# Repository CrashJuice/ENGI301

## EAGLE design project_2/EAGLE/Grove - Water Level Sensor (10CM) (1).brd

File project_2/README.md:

PocketBeagle-Based PCB Project

Overview

This project involves designing and building a PCB around the PocketBeagle to implement a system with specific features and functionality. The goal is to integrate multiple components, such as LEDs, sensors, and input devices, into a compact, reliable circuit for demonstration and testing purposes.

Features

PocketBeagle Integration: Serves as the microcontroller for the project.

Custom PCB Design: A compact and efficient layout that includes connections for multiple hardware components.

Visual Indicators: Use of LEDs for feedback and status indication.

User Interaction: Includes buttons or other input methods to interface with the system.

Components

PocketBeagle: Acts as the central processing unit.

LEDs: Provide visual feedback for system status.

Button(s): Allow for user interaction with the system.

Buzzer (Optional): Can be included for auditory feedback.

Additional Sensors/Modules: Depending on the specific use case, additional sensors can be integrated.

Functionality

Hardware Integration:

All components are connected to the PocketBeagle via GPIO pins or other interfaces (e.g., I2C, SPI, UART).

The PCB provides a stable and organized connection environment.

Feedback System:

LEDs indicate system states such as power, activity, or errors.

Buttons allow users to trigger specific actions or reset the system.

Software Control:

The PocketBeagle runs scripts to manage hardware components.

Scripts handle real-time inputs and outputs for smooth operation.

PCB Design

Schematic:

The schematic includes all connections between components, showing how they interface with the PocketBeagle.

Important connections are labeled (e.g., P2_4, P2_6 for LEDs).

Board Layout:

The PCB layout is designed for compactness and minimal signal interference.

Includes clear labels for pin headers and component placement.

Acknowledgements:

I used Groove Water Sensor base PCB design to create mine link to their website here: https://wiki.seeedstudio.com/Grove-Water_Sensor/

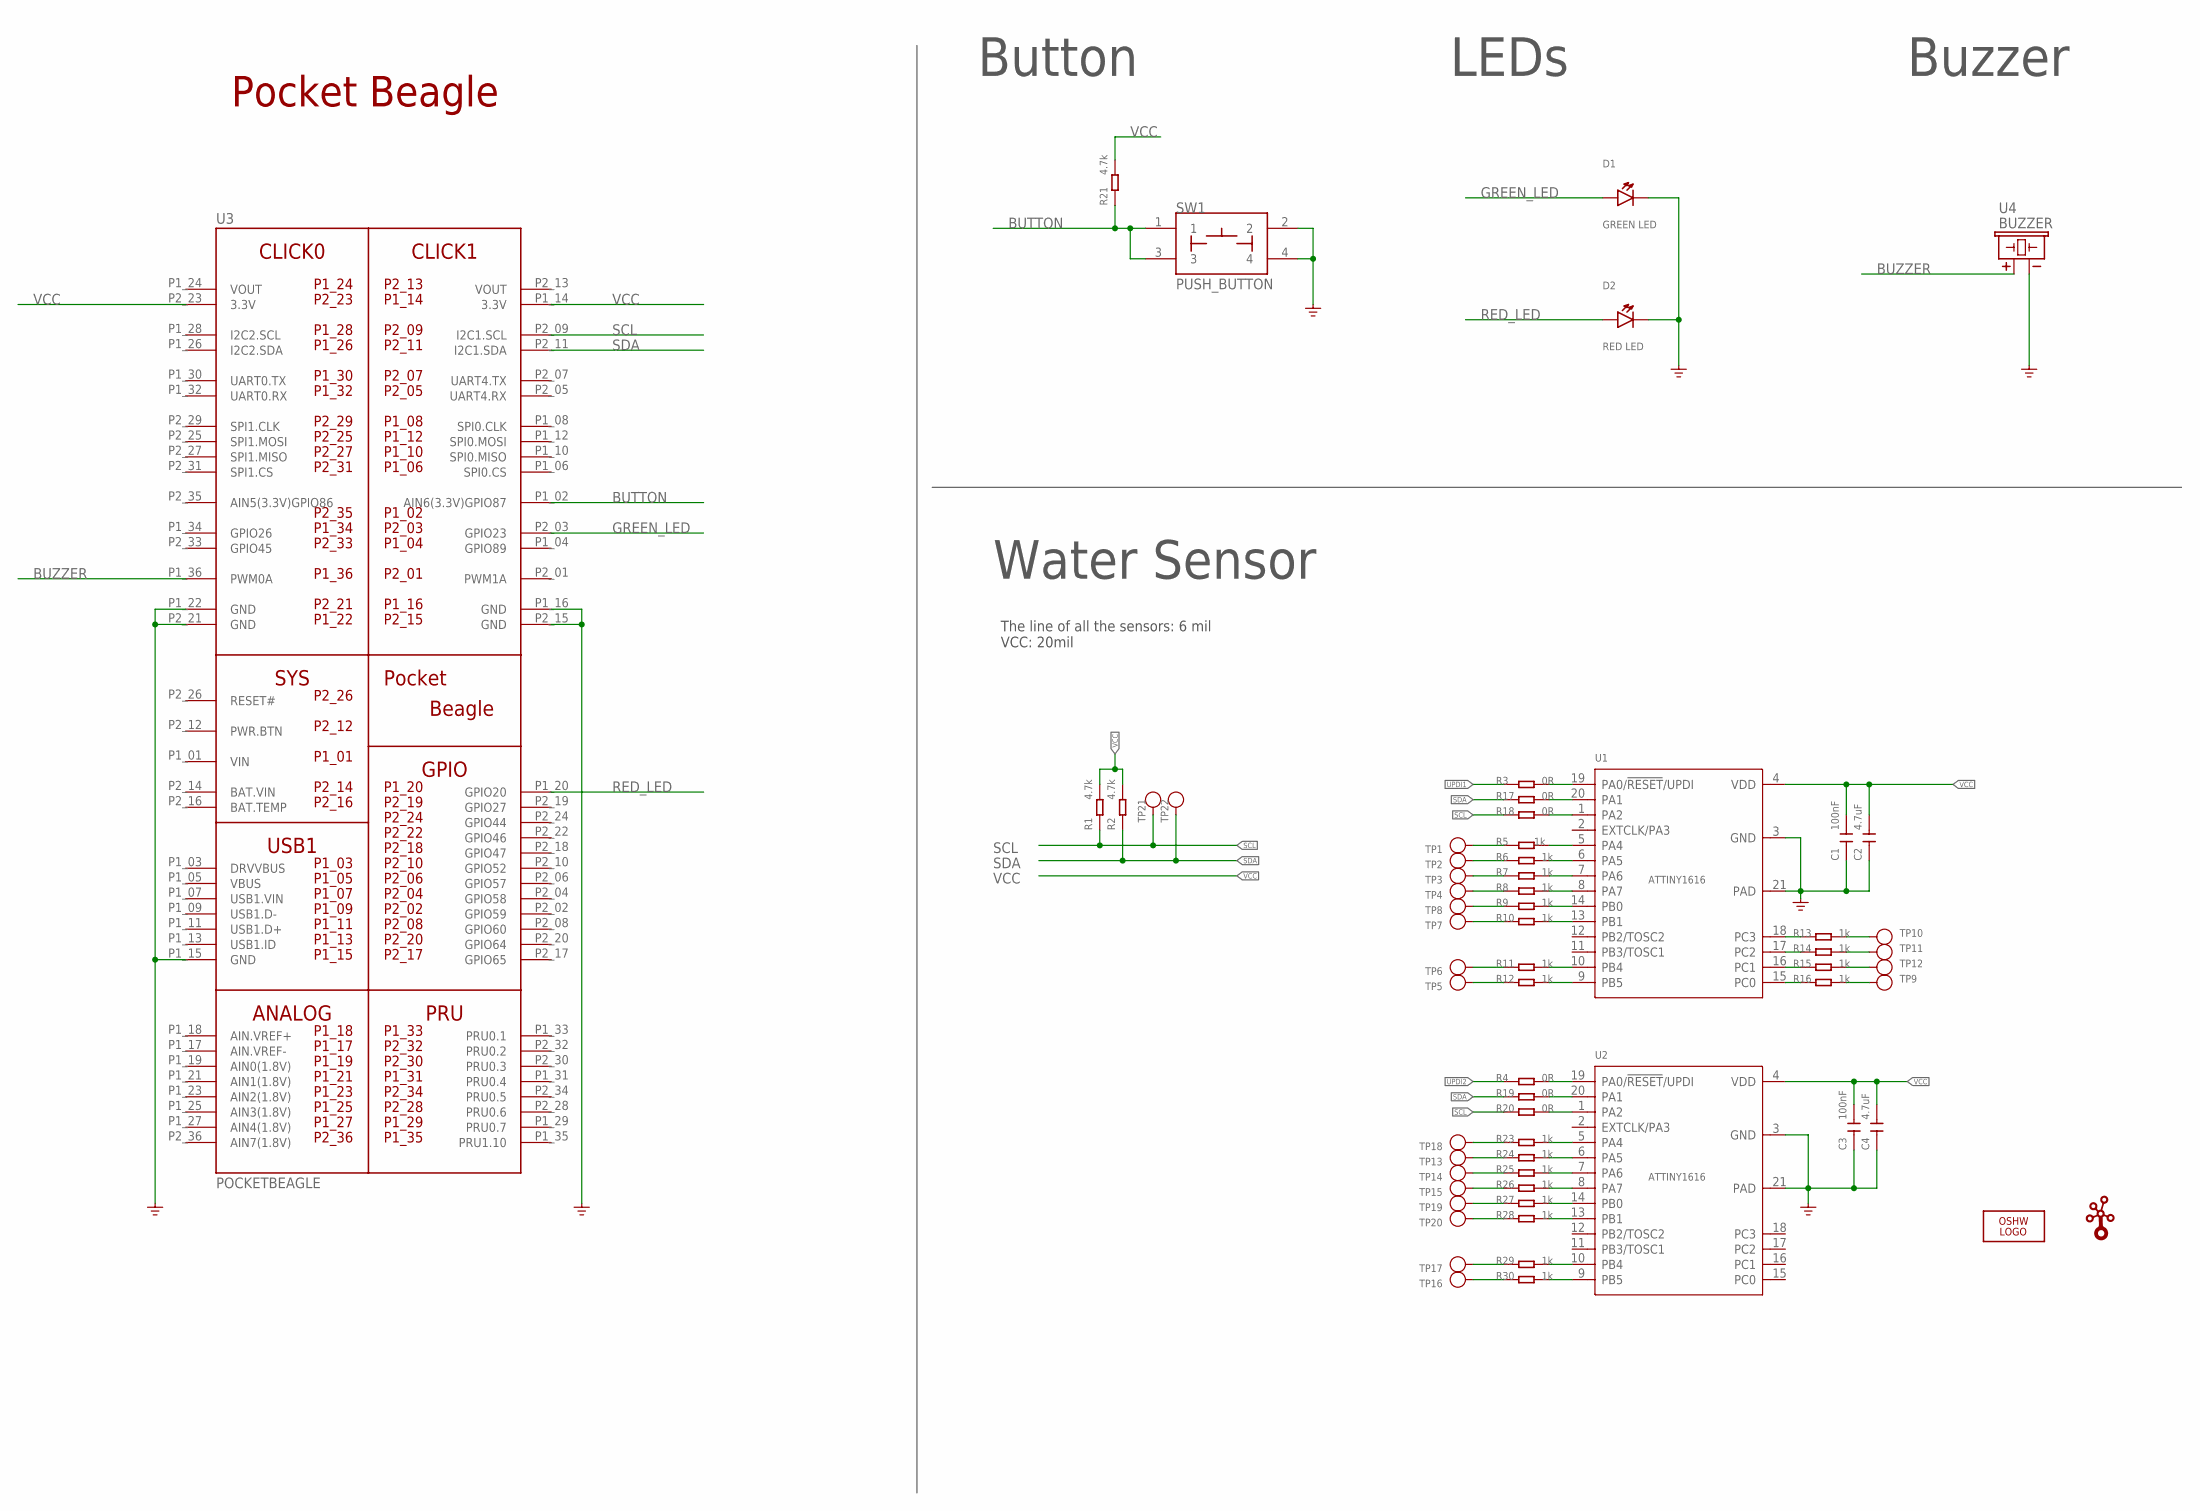
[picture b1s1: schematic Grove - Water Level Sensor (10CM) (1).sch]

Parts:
C1, C3: 100nF; C0402
C2, C4: 4.7uF; C0402
D1: GREEN LED; EIA-STD
D2: RED LED; EIA-STD
LOGO2: LOGO-OSHW-FILLX0200-NT; OSHW_FILLX200_NOTEXT
R1, R2, R21: 4.7k; R0402
R3, R4, R17, R18, R19, R20: 0R; R0402
R5, R6, R7, R8, R9, R10, R11, R12, R13, R14, R15, R16, R23, R24, R25, R26, R27, R28, R29, R30: 1k; R0402
SW1: PUSH_BUTTON; BUTTON_12.5MM
TP1, TP2, TP3, TP4, TP5, TP6, TP7, TP8, TP9, TP10, TP11, TP12, TP13, TP14, TP15, TP16, TP17, TP18, TP19, TP20: senser; TP-80X40MIL-NOSTOP
TP21, TP22: test; TP-D45MIL
U1, U2: ATTINY1616; VQFN20-0.4-3X3MM
U3: POCKETBEAGLE
U4: BUZZER; BUZZER_6.5MM
U$2: LOGO-GROVE; GROVE-SILK-BIG

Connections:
BAT.VIN: U3.P2_14 (BAT.VIN)
BUTTON: R21.1, SW1.1, SW1.3, U3.P1_02 (AIN6(3.3V)GPIO87)
BUZZER: U3.P1_36 (PWM0A), U4.+
GND: C1.1, C2.1, C3.1, C4.1, D1.CATHODE, D2.CATHODE, SW1.2, SW1.4, U1.3 (GND), U1.21 (PAD), U2.3 (GND), U2.21 (PAD), U3.P1_15 (GND), U3.P1_16 (GND), U3.P1_22 (GND), U3.P2_15 (GND), U3.P2_21 (GND), U4.-
GREEN_LED: D1.ANODE, U3.P2_03 (GPIO23)
unnamed: R3.2, U1.19 (PA0/!RESET!/UPDI)
unnamed: R4.2, U2.19 (PA0/!RESET!/UPDI)
unnamed: R17.2, U1.20 (PA1)
unnamed: R18.2, U1.1 (PA2)
unnamed: R19.2, U2.20 (PA1)
unnamed: R20.2, U2.1 (PA2)
unnamed: R23.1, TP18.P$1
unnamed: R29.1, TP17.P$1
unnamed: R30.2, U2.9 (PB5)
unnamed: R29.2, U2.10 (PB4)
unnamed: R28.2, U2.13 (PB1)
unnamed: R27.2, U2.14 (PB0)
unnamed: R26.2, U2.8 (PA7)
unnamed: R25.2, U2.7 (PA6)
unnamed: R24.2, U2.6 (PA5)
unnamed: R23.2, U2.5 (PA4)
unnamed: R28.1, TP20.P$1
unnamed: R27.1, TP19.P$1
unnamed: R5.2, U1.5 (PA4)
unnamed: R6.2, U1.6 (PA5)
unnamed: R7.2, U1.7 (PA6)
unnamed: R8.2, U1.8 (PA7)
unnamed: R9.2, U1.14 (PB0)
unnamed: R10.2, U1.13 (PB1)
unnamed: R25.1, TP14.P$1
unnamed: R11.2, U1.10 (PB4)
unnamed: R12.2, U1.9 (PB5)
unnamed: R13.1, U1.18 (PC3)
unnamed: R14.1, U1.17 (PC2)
unnamed: R15.1, U1.16 (PC1)
unnamed: R16.1, U1.15 (PC0)
unnamed: R11.1, TP6.P$1
unnamed: R12.1, TP5.P$1
unnamed: R26.1, TP15.P$1
unnamed: R30.1, TP16.P$1
unnamed: R10.1, TP7.P$1
unnamed: R9.1, TP8.P$1
unnamed: R24.1, TP13.P$1
unnamed: R13.2, TP10.P$1
unnamed: R14.2, TP11.P$1
unnamed: R15.2, TP12.P$1
unnamed: R5.1, TP1.P$1
unnamed: R6.1, TP2.P$1
unnamed: R7.1, TP3.P$1
unnamed: R8.1, TP4.P$1
unnamed: R16.2, TP9.P$1
RED_LED: D2.ANODE, U3.P1_20 (GPIO20)
SCL: R1.1, R18.1, R20.1, TP21.T, U3.P2_09 (I2C1.SCL)
SDA: R2.1, R17.1, R19.1, TP22.T, U3.P2_11 (I2C1.SDA)
UPDI1: R3.1
UPDI2: R4.1
VCC: C1.2, C2.2, C3.2, C4.2, R1.2, R2.2, R21.2, U1.4 (VDD), U2.4 (VDD), U3.P1_14 (3.3V), U3.P2_23 (3.3V)
VIN: U3.P1_01 (VIN)
VOUT: U3.P1_24 (VOUT), U3.P2_13 (VOUT)

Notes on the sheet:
The line of all the sensors: 6 mil VCC: 20mil
Water Sensor
Button
LEDs
Buzzer
Pocket Beagle

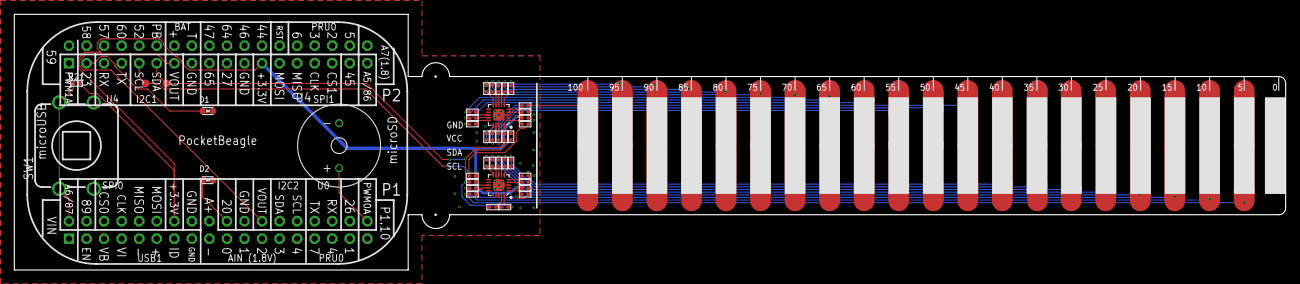
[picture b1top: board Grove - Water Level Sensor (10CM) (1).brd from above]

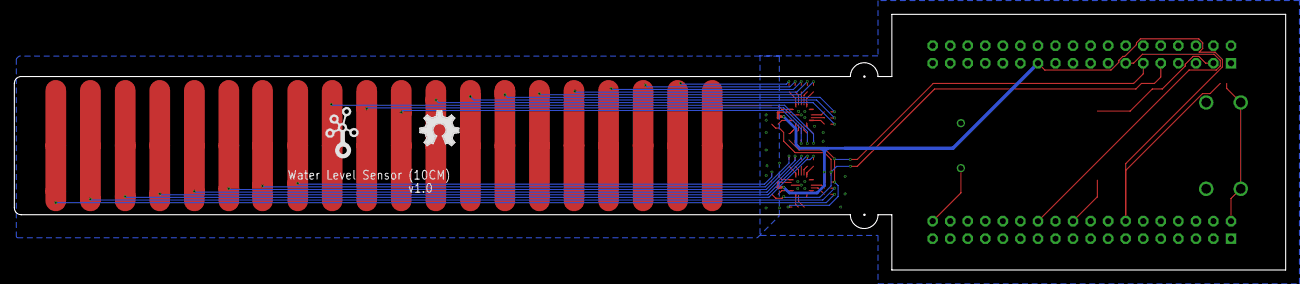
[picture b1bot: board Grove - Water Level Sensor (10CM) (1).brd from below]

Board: 2 copper layers, 184.0 x 37.0 mm, 64 parts (2 on the bottom side), 55 nets.

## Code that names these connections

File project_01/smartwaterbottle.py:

# -*- coding: utf-8 -*-
"""
--------------------------------------------------------------------------
Aquatrac smart water bottle
--------------------------------------------------------------------------
License:   
Copyright 2024 Juan Aizprua

Redistribution and use in source and binary forms, with or without 
modification, are permitted provided that the following conditions are met:

1. Redistributions of source code must retain the above copyright notice, this 
list of conditions and the following disclaimer.

2. Redistributions in binary form must reproduce the above copyright notice, 
this list of conditions and the following disclaimer in the documentation 
and/or other materials provided with the distribution.

3. Neither the name of the copyright holder nor the names of its contributors 
may be used to endorse or promote products derived from this software without 
specific prior written permission.

THIS SOFTWARE IS PROVIDED BY THE COPYRIGHT HOLDERS AND CONTRIBUTORS "AS IS" 
AND ANY EXPRESS OR IMPLIED WARRANTIES, INCLUDING, BUT NOT LIMITED TO, THE 
IMPLIED WARRANTIES OF MERCHANTABILITY AND FITNESS FOR A PARTICULAR PURPOSE ARE 
DISCLAIMED. IN NO EVENT SHALL THE COPYRIGHT HOLDER OR CONTRIBUTORS BE LIABLE 
FOR ANY DIRECT, INDIRECT, INCIDENTAL, SPECIAL, EXEMPLARY, OR CONSEQUENTIAL 
DAMAGES (INCLUDING, BUT NOT LIMITED TO, PROCUREMENT OF SUBSTITUTE GOODS OR 
SERVICES; LOSS OF USE, DATA, OR PROFITS; OR BUSINESS INTERRUPTION) HOWEVER 
CAUSED AND ON ANY THEORY OF LIABILITY, WHETHER IN CONTRACT, STRICT LIABILITY, 
OR TORT (INCLUDING NEGLIGENCE OR OTHERWISE) ARISING IN ANY WAY OUT OF THE USE 
OF THIS SOFTWARE, EVEN IF ADVISED OF THE POSSIBILITY OF SUCH DAMAGE.
--------------------------------------------------------------------------
This file provides an interface to a PWM controllered buzzer.
  - Ex:  https://www.adafruit.com/product/1536


Combines water level sensor, buzzer, button, and leds together to create a program that helps you keep track of how much water you are drinking and if you 
are on track for the amount you should be drinking in a day.

"""








from button import Button
from led import LED
from buzzer import Buzzer
from waterlevelsensor import get_water_level
import Adafruit_BBIO.GPIO as GPIO
import time
import threading 



RED_LED_PIN = "P2_4"  # Red LED pin
GREEN_LED_PIN = "P2_6"  # Green LED pin
BUTTON_PIN = "P2_2"  # Button pin
BUZZER_PIN = "P2_1"  # Buzzer pin

red_led = LED(pin=RED_LED_PIN, low_off=True)  # Red LED, off when LOW
green_led = LED(pin=GREEN_LED_PIN, low_off=True)  # Green LED, off when LOW

# Initialize Button
button = Button(pin=BUTTON_PIN, sleep_time=0.1, active_low=True)

buzzer = Buzzer(pin=BUZZER_PIN) 

# Target water goal
TARGET_WATER = 100  # Target water intake in %

previous_water_level = 0.0  # Stores the last recorded water level
water_drunk = 0.0           # Amount of water consumed in percentage
faillasttime = False  # Tracks if user failed previously
minsections = 0  # Tracks the number of 30-minute sections

# Global variable to check progress (shared between monitor and button press)
def check_user_progress():
    global minsections, water_drunk, faillasttime
    
    required_intake = (minsections / 32) * TARGET_WATER  # Calculate required intake for this section
    
    if water_drunk >= required_intake:
        green_led.on()  # On track
        red_led.off()   # Turn off red LED
        time.sleep(10)
        green_led.off()  # Turn off green LED after 10 seconds
    else:
        green_led.off()  # Turn off green LED
        red_led.on()     # Behind
        time.sleep(10)
        red_led.off()    # Turn off red LED after 10 seconds

        if faillasttime:
            buzzer.play(800, 2.0, False)  # Play buzzer for 2 seconds
            time.sleep(2.0)
            buzzer.play(980, 2.0, True)   # Play buzzer again for 2 seconds
            time.sleep(2.0)

        faillasttime = True  # Mark that they failed this time

def button_press_check():
    """ Check button press and call check_user_progress() if pressed """
    if button.is_pressed():
        print("Button Pressed!")
        check_user_progress()

def check_water_level():
    global previous_water_level, water_drunk
    
    current_water_level = get_water_level()  # Get the current water level
    
    if current_water_level is not None:
        # If the current water level is lower than the previous one, calculate the difference
        if current_water_level < previous_water_level:
            water_drunk += previous_water_level - current_water_level  # Add the difference to water drunk
            
        previous_water_level = current_water_level  # Update previous water level to current
        
        print(f"Current water level: {current_water_level:.2f}%")
        print(f"Water drank: {water_drunk:.2f}%")
    else:
        print("Failed to get water level.")

def monitor_water_level():
    global minsections, faillasttime, water_drunk 
    
    while True:
        check_water_level()  # Call the function to check the user's water intake
        
        # Calculate the target water intake for this 30-minute interval
        required_intake = (minsections / 32) * TARGET_WATER  # Target for the current 30-minute section
        
        if water_drunk >= required_intake:
            # The user is on track, reset faillasttime if they were previously behind
            if faillasttime:
                faillasttime = False  # Reset if user caught up
            print(f"You're on track! You've consumed {water_drunk:.2f}%.")
        else:
            # The user is behind on their goal
            red_led.on()  # Behind
            time.sleep(5)
            red_led.off()
            print(f"You're behind! You've consumed {water_drunk:.2f}%.")
            if faillasttime:
                buzzer.play(800, 2.0, False)      # Play buzzer for 1 second
                time.sleep(2.0)
                buzzer.play(980, 2.0, True)       # Play buzzer for 1 second
                time.sleep(2.0)   
            faillasttime = True  # Mark that they failed this time
        
        # Increment the 30-minute sections counter
        minsections += 1
        
        # Wait for 30 minutes before checking again
        time.sleep(30)  

def main():
    # Start monitor_water_level function in a separate thread
    monitor_thread = threading.Thread(target=monitor_water_level)
    monitor_thread.daemon = True  # Daemonize the thread so it exits when the program exits
    monitor_thread.start()
    
    while True:
        button_press_check()  # Continuously check for button press
        time.sleep(0.1)  # Small delay to prevent overloading the CPU

if __name__ == "__main__":
    main()

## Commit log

2024-09-25 Updating README.md
2024-10-01 Added proposal
2024-10-02 Added support for new operators and Python 2 compatibility
2024-10-21 Updating Simple Calc
2024-10-21 Created blinking file
2024-10-21 adding button
2024-12-20 Create test
2024-12-20 Rename Grove - Water Level Sensor (10CM) (1).brd to SmartWaterBottle.brd
2024-12-20 Rename Grove - Water Level Sensor (10CM) (1).sch to SmartWaterBottle.sch
